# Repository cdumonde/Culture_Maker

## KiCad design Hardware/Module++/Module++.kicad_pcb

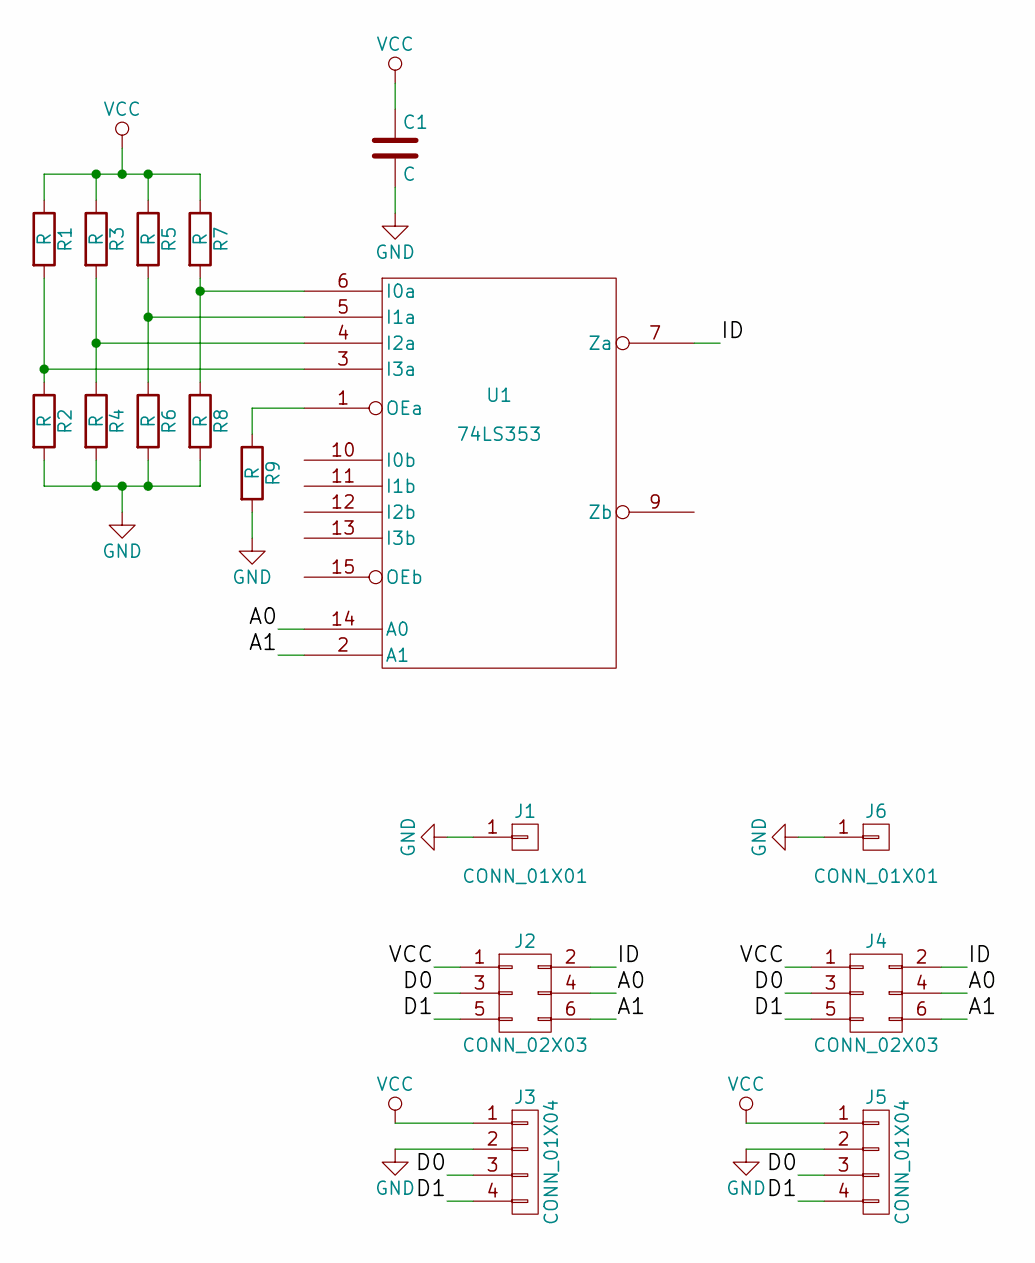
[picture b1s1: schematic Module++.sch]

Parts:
C1: C; C_0603_HandSoldering
J1, J6: CONN_01X01; Pin_Header_Straight_1x01_Pitch2.54mm
J2, J4: CONN_02X03; Pin_Header_Straight_2x03_Pitch2.54mm
J3, J5: CONN_01X04; Pin_Header_Straight_1x04_Pitch2.54mm
R1, R2, R3, R4, R5, R6, R7, R8, R9: R; R_0603_HandSoldering
U1: 74LS353; TSSOP-16_4.4x5mm_Pitch0.65mm

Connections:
/A0: J2.4, J4.4, U1.14 (A0)
/A1: J2.6, J4.6, U1.2 (A1)
/D0: J2.3, J3.3, J4.3, J5.3
/D1: J2.5, J3.4, J4.5, J5.4
/ID: J2.2, J4.2, U1.7 (Za)
GND: C1.2, J1.1, J3.2, J5.2, J6.1, R2.2, R4.2, R6.2, R8.2, R9.2, U1.8 (GND)
unnamed: R1.2, R2.1, U1.3 (I3a)
unnamed: R3.2, R4.1, U1.4 (I2a)
unnamed: R5.2, R6.1, U1.5 (I1a)
unnamed: R7.2, R8.1, U1.6 (I0a)
unnamed: R9.1, U1.1 (OEa)
VCC: C1.1, J2.1, J3.1, J4.1, J5.1, R1.1, R3.1, R5.1, R7.1, U1.16 (VCC)

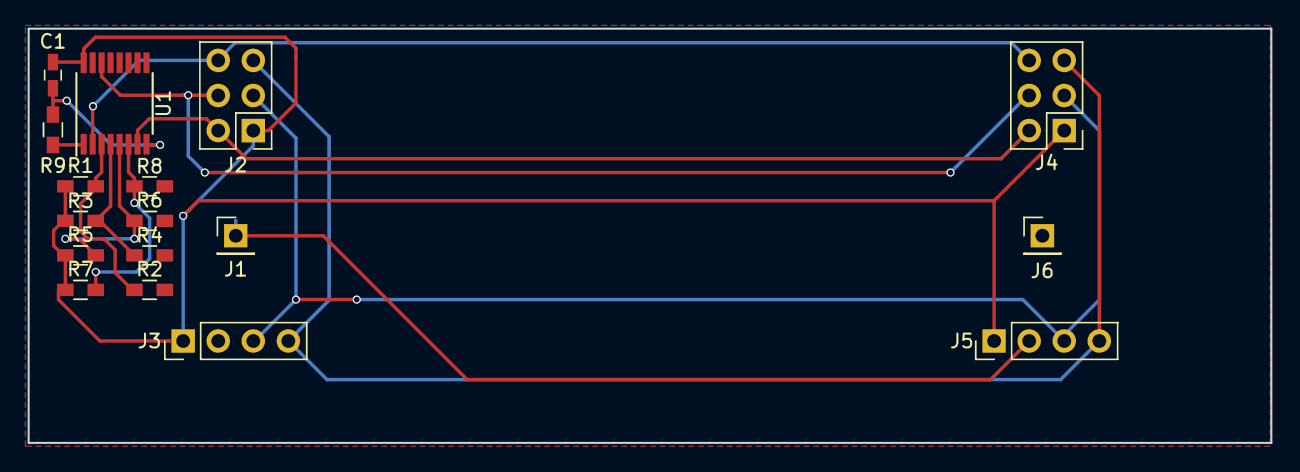
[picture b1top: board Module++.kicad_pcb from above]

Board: 2 copper layers, 90.0 x 30.0 mm, 17 parts (0 on the bottom side), 12 nets.

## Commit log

2017-03-16 Add some directory
2017-03-16 add empty makefile
2017-03-16 Added imgui
2017-03-16 Created department directories
2017-03-16 Removed imgui examples
2017-03-16 Pushed readme on all folders
2017-03-16 Test the lib
2017-03-16 Add files via upload
    Sensors test arduino code
2017-03-19 Added gitattributes to fix (hopefully) the line ending errors on Windows
2017-03-19 Fixed the Interface_midi Makefile
2017-03-19 Added a "virtual" midi keyboard
2017-03-19 Updated virtual_keyboard readme
2017-03-20 Removed rtmidi doc (because it's annoying)
2017-03-21 Fixed note_on & note_off message values
2017-03-21 Added minimal gitignore
2017-03-21 Added a "midi parser" (check README.md for desc.)
2017-03-30 tri et dossiers renommés
2017-03-30 add Pad class
2017-03-30 Log fichier compilation sous mac OS
    Log fichier compilation sous mac OS.
2017-03-30 Add Control class
    Control.h
    Control.cpp
2017-03-30 Add some features of Pad class
2017-03-30 Control -> Controller
    Control -> Controller
2017-03-30 Update Controller
    Suite du code. Début des codes sur Save et Load dans les .mod
2017-04-02 Controller Update + Test
    Avancement de la classe Controller.
    Création d’un fichier main de test.
    Conversion uChar -> string hexadecimal
    Test de la creation de *.mod
    Modification du makefile pour tester class Controller
2017-04-02 Controller Update & Load function
    Mises a jour de Controller,
    Debugage de la méthode loadController,
    Ajout d’un #define DEBUG,
    Manipulation des conversions string/hex vers uChar.
2017-04-03 Test des capteurs
2017-04-06 Add Controller source and header to Pad folder
2017-04-06 Commit test
    Test pour Debug le Git de Baptiste
    Suppression .log
2017-04-06 fck gitattributes
2017-04-06 Gitignore
2017-04-06 Supress Control sources
2017-04-06 Controller Update
2017-04-06 examples
2017-04-06 Début de configController
2017-04-06 Created Kicad project
2017-04-06 Revert "Corrected Controller class"
    This reverts commit 3f65afcdb4c5dee76876981e0cfa8ed56ec50be9.
2017-04-06 Corrected Controller class
2017-04-06 Revert "Revert "Corrected Controller class""
    This reverts commit 544c692aacb52d7f1229a31f3c185a7283d1f4f0.
2017-04-06 Add function class and Types header which is used to store all important enum and defitions of the project
2017-04-06 Cleanup of Controller class
2017-04-06 More code beautification
2017-04-13 Hardware: Add Module PCB layout
2017-04-13 Hardware: started base PCB structure
2017-04-13 Add function sources
2017-04-13 sprite for software
    lots of pictures...
2017-04-13 Hardware: Add Module++ PCB layout for sliders
2017-04-15 Add shortcut management function in Function.h/cpp
2017-04-16 prepare for Windows shortcut management
2017-04-27 Finish Linux shortcut management
2017-04-27 Finish Controller class and start Pad class
2017-04-27 Hardware: Fix missing VCC connection
2017-04-27 Base schematics almost done
2017-05-04 dessin vierge
2017-05-08 Hardware: Start the base PCB
